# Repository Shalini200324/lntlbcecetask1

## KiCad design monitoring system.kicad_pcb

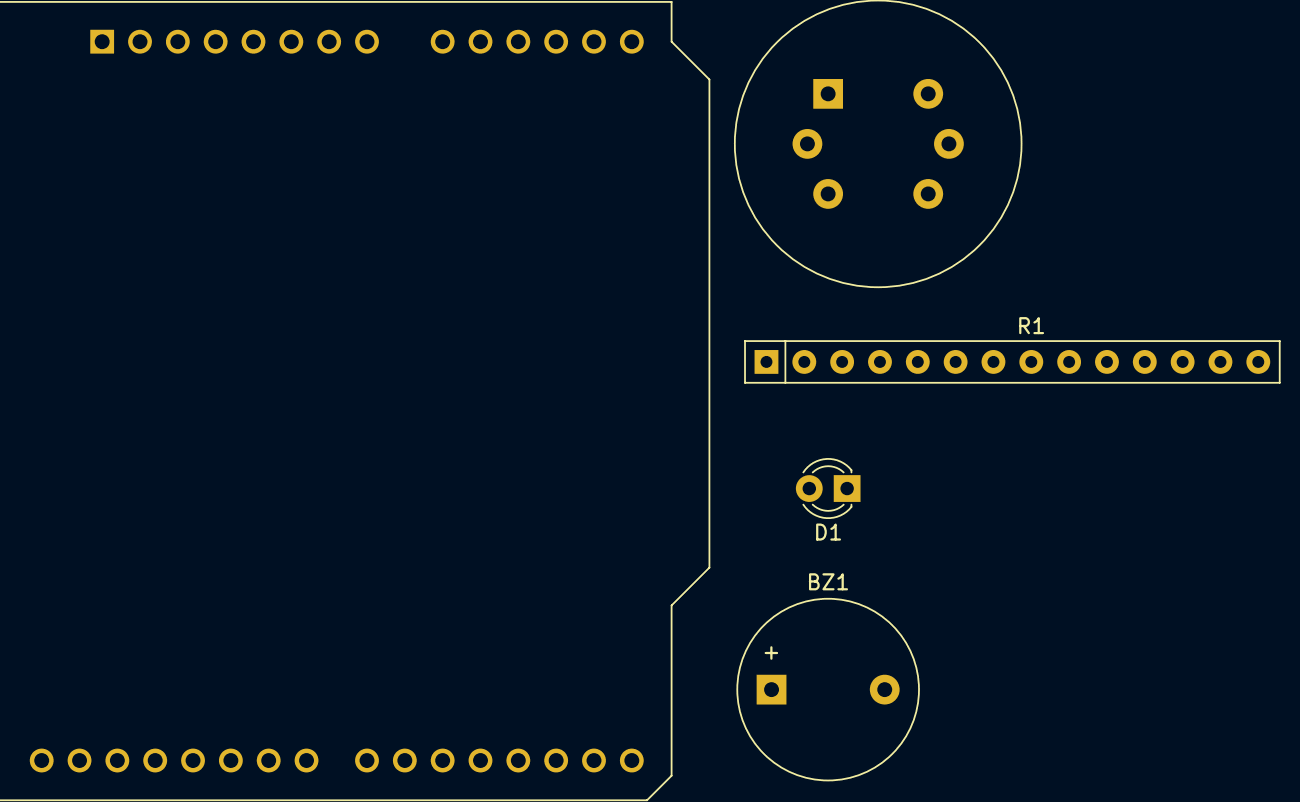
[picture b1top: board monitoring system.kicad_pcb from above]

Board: 2 copper layers, 5 parts (0 on the bottom side), 6 nets, no tracks yet.

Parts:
A1: Arduino_UNO_R2
BZ1: Buzzer; Buzzer_12x9.5RM7.6
D1: LED; LED_D3.0mm
R1: R; R_Array_SIP14
U1: MQ-6

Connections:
unnamed: A1.5 (+5V), U1.2 (VH+)
unnamed: A1.9 (A0), U1.6 (A1)
unnamed: A1.25 (D10), R1.2
unnamed: A1.28 (D13), BZ1.1 (+)
unnamed: A1.7 (GND), BZ1.2 (-), D1.1 (K), U1.5 (VH-)
unnamed: D1.2 (A), R1.1
